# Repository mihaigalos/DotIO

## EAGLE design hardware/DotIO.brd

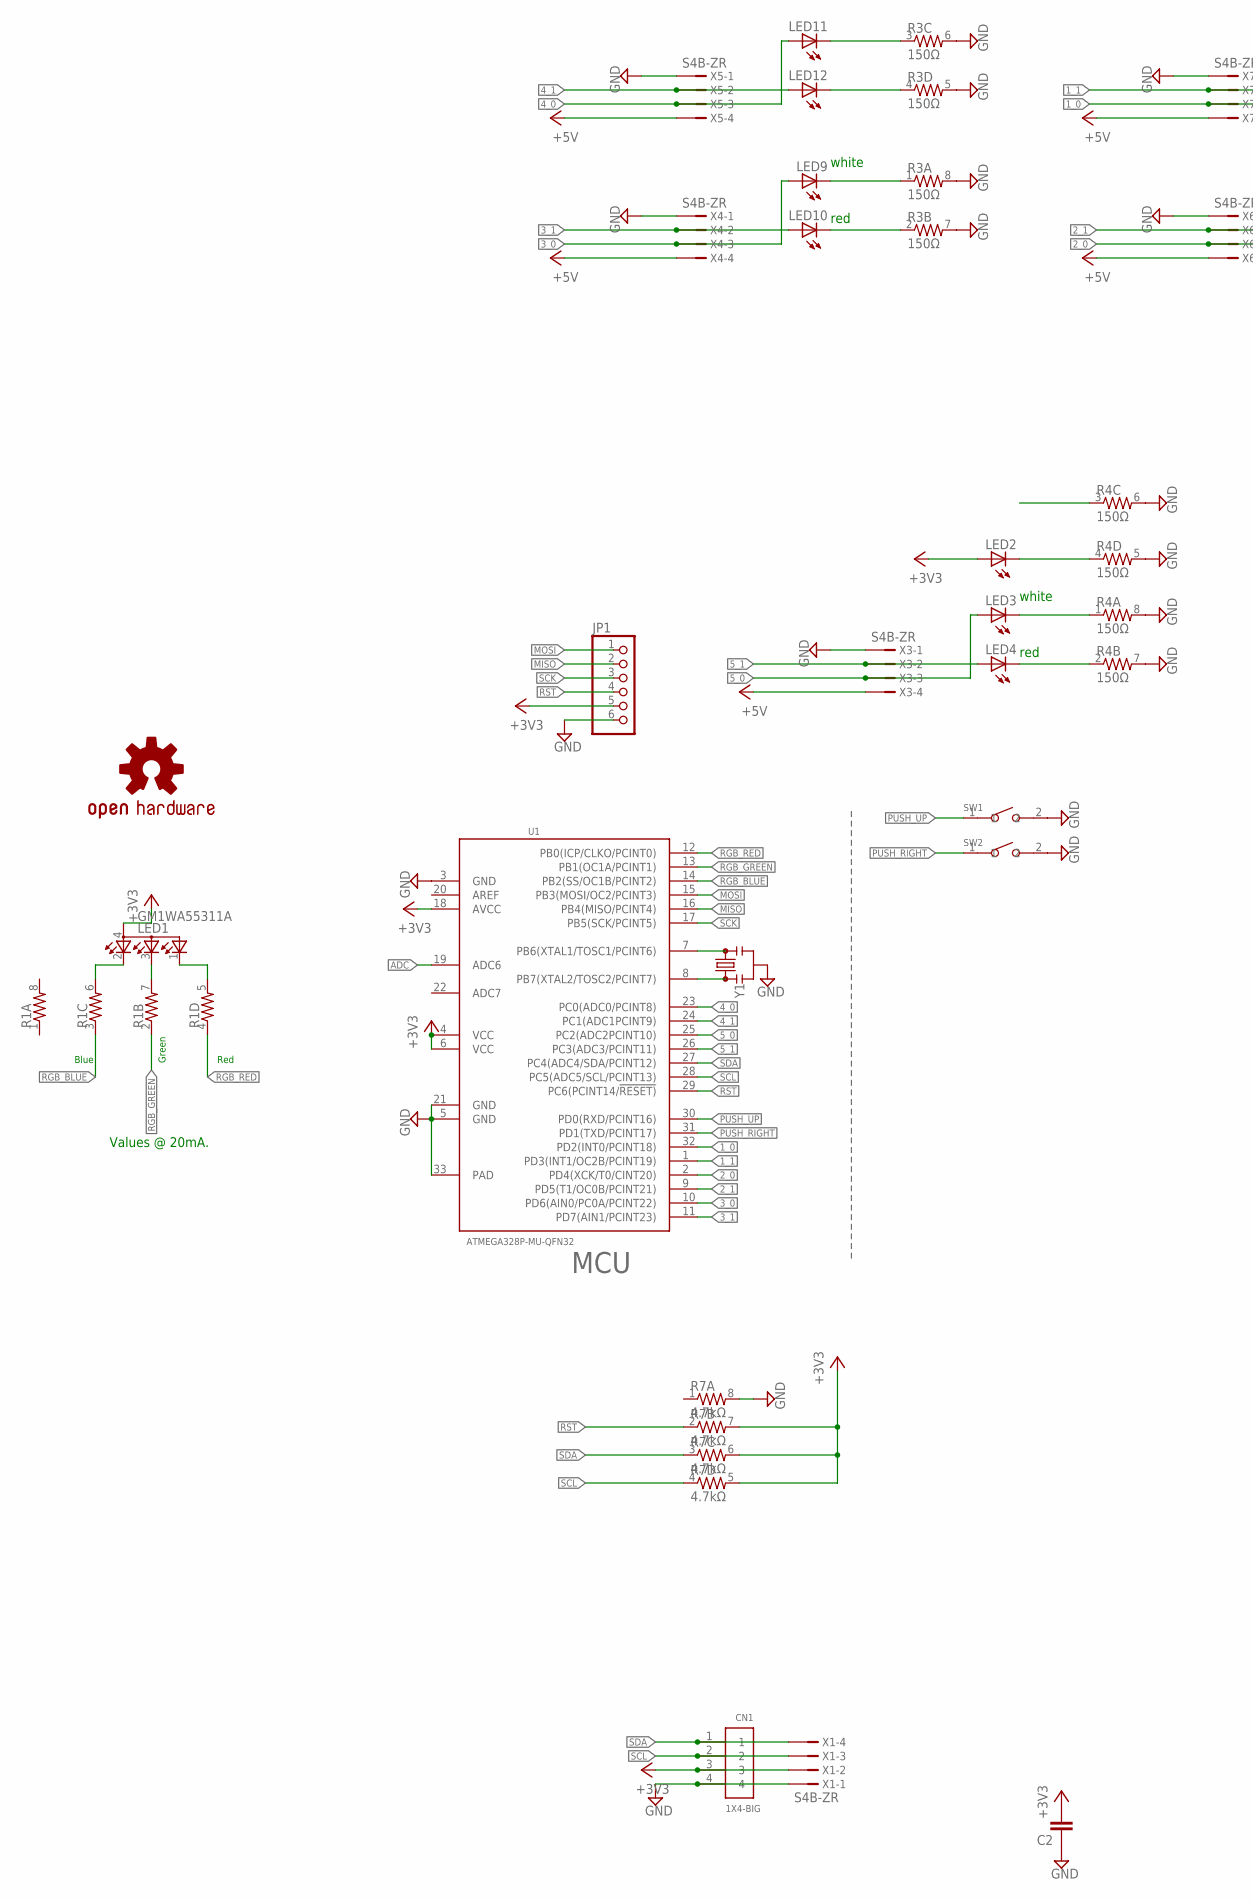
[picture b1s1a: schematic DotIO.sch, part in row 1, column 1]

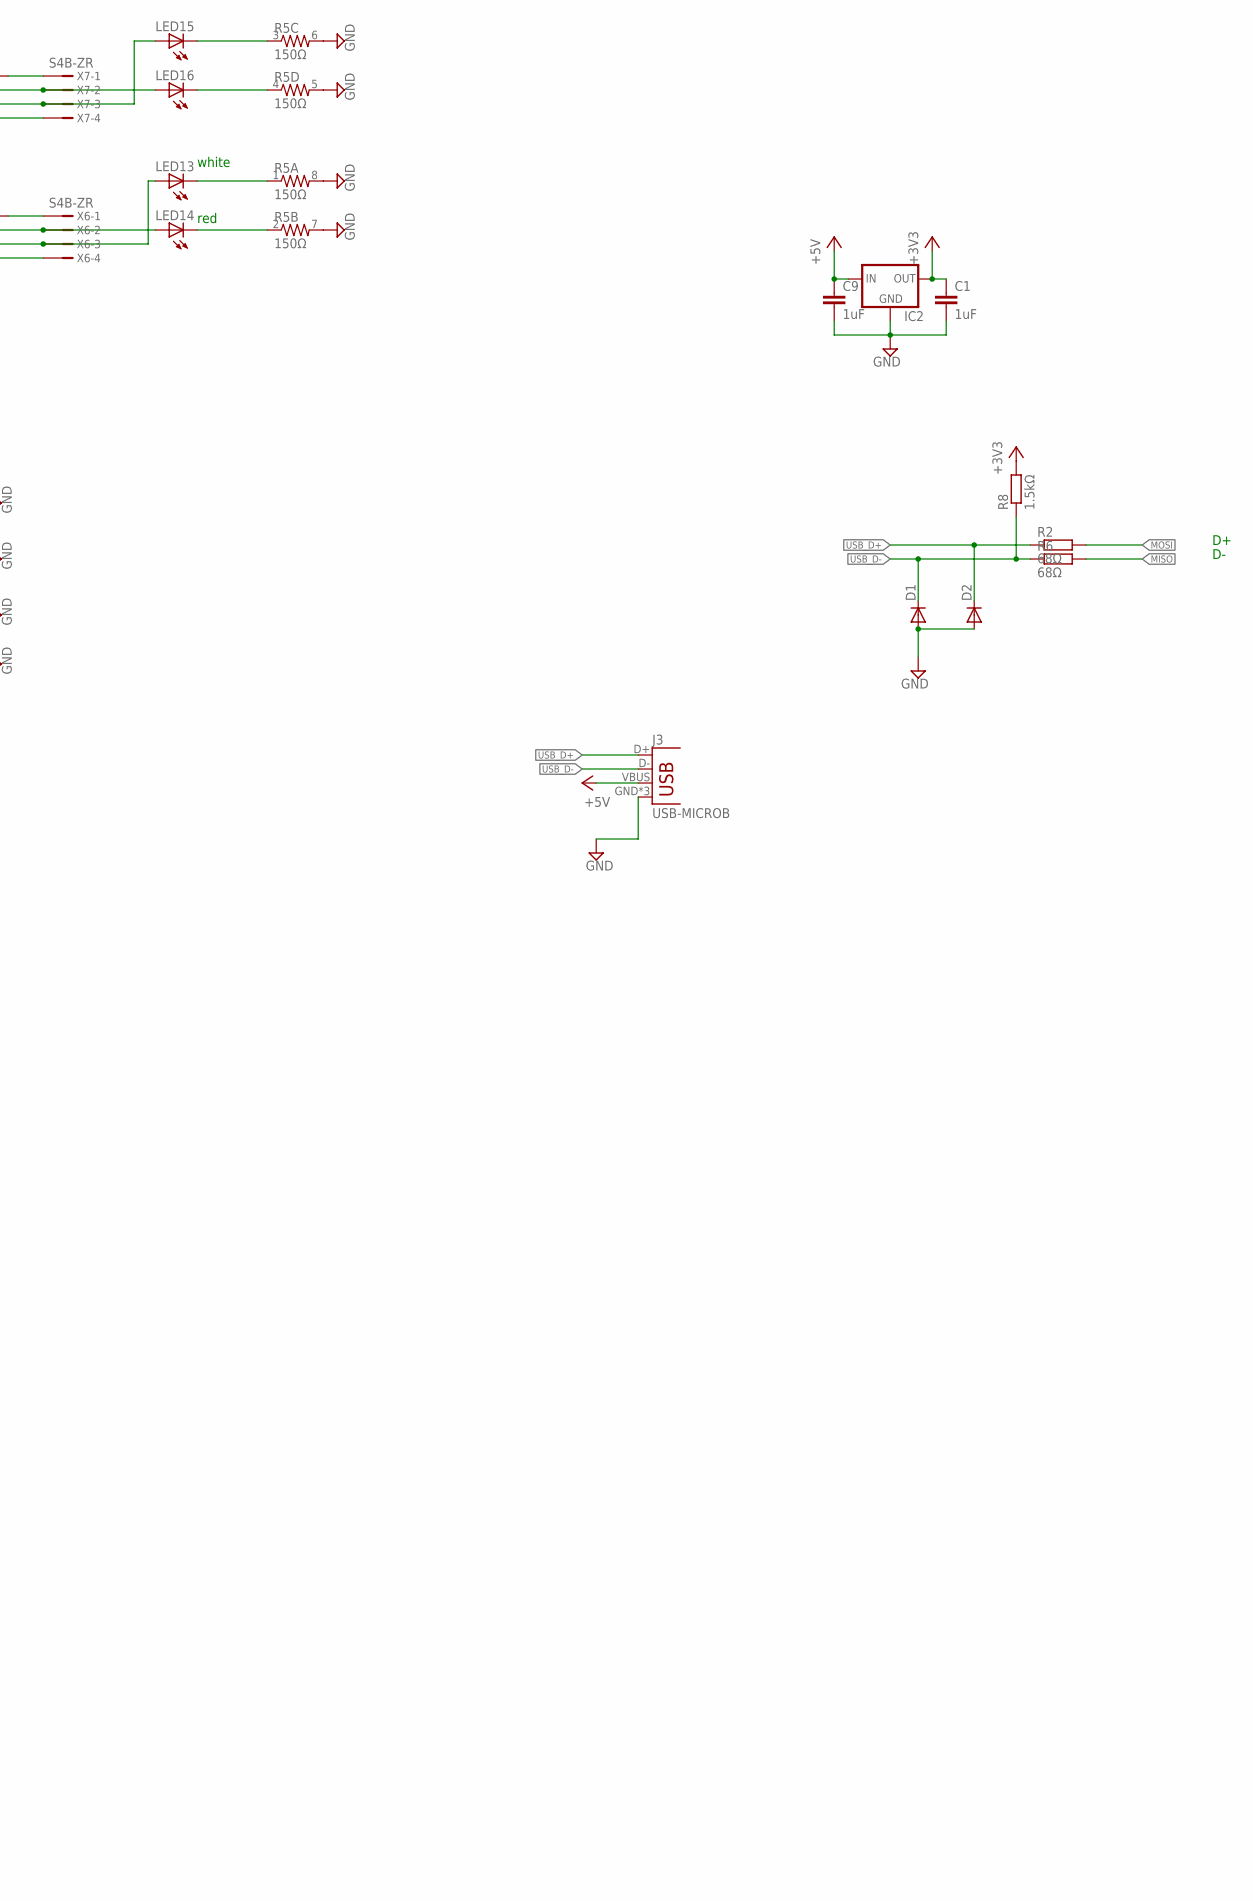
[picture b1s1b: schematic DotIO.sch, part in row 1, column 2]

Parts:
C1, C9: 1uF; C0603
C2: C-EUC3216; C3216
CN1: 1X4-BIG; 1X04-BIG
D1, D2: DIODE-SOD523; SOD523
IC2: MCP1700TT; SOT-23
J3: USB-MICROB
JP1: PINHD-1X6; 1X06
LED1: GM1WA55311A
LED2, LED3, LED4, LED9, LED10, LED11, LED12, LED13, LED14, LED15, LED16: LED0603; LED-0603
LOGO1: OSHW-LOGOS; OSHW-LOGO-S
R1: RESISTOR-ARRAY0603-ARV; 0603-ARV
R2, R6: 68Ω; R0603
R3, R4, R5: 150Ω; 0603-ARV
R7: 4.7kΩ; 0603-ARV
R8: 1.5kΩ; R0603
SW1, SW2: SMD-BUTTON(2P-6.0X3.0X2.5MM)-DHT-1163S; SW2-4.0-6.0X3.0X2.5MM
U1: ATMEGA328P-MU-QFN32; QFN32G-0.5-5X5MM
X1, X3, X4, X5, X6, X7: S4B-ZR
Y1: RESONATORSMD-3.2X1.3; RESONATOR-SMD-3.2X1.3

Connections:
1_0: LED15.A, U1.32 (PD2(INT0/PCINT18)), X7.3
1_1: LED16.A, U1.1 (PD3(INT1/OC2B/PCINT19)), X7.2
2_0: LED13.A, U1.2 (PD4(XCK/T0/CINT20)), X6.3
2_1: LED14.A, U1.9 (PD5(T1/OC0B/PCINT21)), X6.2
3_0: LED9.A, U1.10 (PD6(AIN0/PC0A/PCINT22)), X4.3
3_1: LED10.A, U1.11 (PD7(AIN1/PCINT23)), X4.2
4_0: LED11.A, U1.23 (PC0(ADC0/PCINT8)), X5.3
4_1: LED12.A, U1.24 (PC1(ADC1PCINT9)), X5.2
5_0: LED3.A, U1.25 (PC2(ADC2PCINT10)), X3.3
5_1: LED4.A, U1.26 (PC3(ADC3/PCINT11)), X3.2
+3V3: C1.1, C2.2, CN1.3, IC2.2 (OUT), JP1.5, LED1.4 (A), LED2.A, R7.5 (2), R7.6 (2), R7.7 (2), R8.2, U1.4 (VCC), U1.6 (VCC), U1.18 (AVCC), X1.2
+5V: C9.1, IC2.3 (IN), J3.VBUS, X3.4, X4.4, X5.4, X6.4, X7.4
ADC: U1.19 (ADC6)
GND: C1.2, C2.1, C9.2, CN1.4, D1.A, D2.A, IC2.1 (GND), J3.GND, J3.MT1 (GND), J3.MT2 (GND), JP1.6, R3.5 (2), R3.6 (2), R3.7 (2), R3.8 (2), R4.5 (2), R4.6 (2), R4.7 (2), R4.8 (2), R5.5 (2), R5.6 (2), R5.7 (2), R5.8 (2), R7.8 (2), SW1.2, SW2.2, U1.3 (GND), U1.5 (GND), U1.21 (GND), U1.33 (PAD), X1.1, X3.1, X4.1, X5.1, X6.1, X7.1, Y1.2
MISO: JP1.2, R6.2, U1.16 (PB4(MISO/PCINT4))
MOSI: JP1.1, R2.2, U1.15 (PB3(MOSI/OC2/PCINT3))
unnamed: LED1.3 (CBLUE), R1.7 (2)
unnamed: LED3.C, R4.1
unnamed: LED1.2 (CRED), R1.6 (2)
unnamed: U1.7 (PB6(XTAL1/TOSC1/PCINT6)), Y1.3
unnamed: LED2.C, R4.4 (1)
unnamed: U1.8 (PB7(XTAL2/TOSC2/PCINT7)), Y1.1
unnamed: LED4.C, R4.2 (1)
unnamed: LED9.C, R3.1
unnamed: LED1.1 (CGREEN), R1.5 (2)
unnamed: LED10.C, R3.2 (1)
unnamed: LED11.C, R3.3 (1)
unnamed: LED12.C, R3.4 (1)
unnamed: LED13.C, R5.1
unnamed: LED14.C, R5.2 (1)
unnamed: LED15.C, R5.3 (1)
unnamed: LED16.C, R5.4 (1)
PUSH_RIGHT: SW2.1, U1.31 (PD1(TXD/PCINT17))
PUSH_UP: SW1.1, U1.30 (PD0(RXD/PCINT16))
RGB_BLUE: R1.3 (1), U1.14 (PB2(SS/OC1B/PCINT2))
RGB_GREEN: R1.2 (1), U1.13 (PB1(OC1A/PCINT1))
RGB_RED: R1.4 (1), U1.12 (PB0(ICP/CLKO/PCINT0))
RST: JP1.4, R7.2 (1), U1.29 (PC6(PCINT14/!RESET))
SCK: JP1.3, U1.17 (PB5(SCK/PCINT5))
SCL: CN1.2, R7.4 (1), U1.28 (PC5(ADC5/SCL/PCINT13)), X1.3
SDA: CN1.1, R7.3 (1), U1.27 (PC4(ADC4/SDA/PCINT12)), X1.4
USB_D+: D2.C, J3.D+, R2.1
USB_D-: D1.C, J3.D-, R6.1, R8.1

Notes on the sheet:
MCU
Values @ 20mA.
Blue
Green
Red
white
red

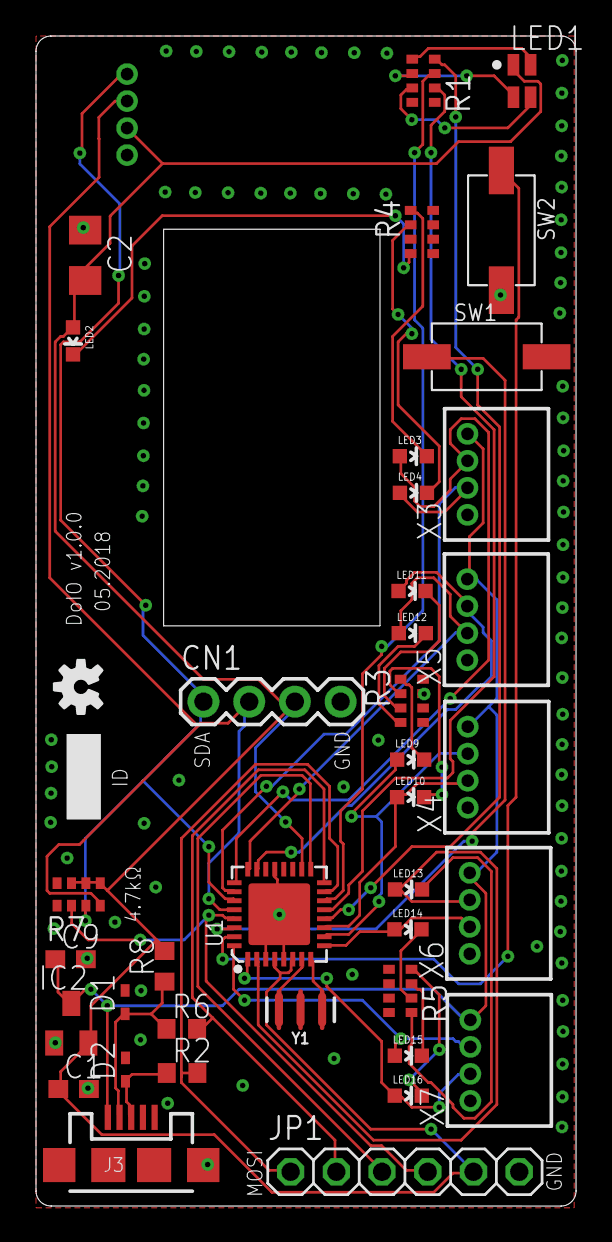
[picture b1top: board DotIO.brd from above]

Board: 2 copper layers, 30.0 x 65.0 mm, 40 parts (1 on the bottom side), 42 nets.

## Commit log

2018-04-07 Add plumbing
2018-04-07 Initial non-usable layout
2018-04-07 Initial routing
2018-04-07 Bind USB to SPI pins
2018-04-07 Flip I2C JST port

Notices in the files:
parts and their libraries:
SparkFun: Licensing: CC v3.0 Share-Alike You are welcome to use this library for commercial purposes.
SparkFun-Clocks: Licensing: Creative Commons ShareAlike 4.0 International - https://creativecommons.org/licenses/by-sa/4.0
